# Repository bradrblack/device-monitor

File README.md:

# Device Monitor

A small box that tells you whether a machine is **on or off** by feeling its
vibration: a sump pump, washer, dryer, AC compressor, well pump, dehumidifier.
An ESP32-C3 SuperMini reads an ADXL346 (or ADXL345) accelerometer and reports
every start and stop, with the run length, to whichever of these you use:

- **Web page on the board** (always on): live state, calibration, settings, log.
- **Home Assistant** over MQTT, found automatically (MQTT Discovery). Enables device status voice alerts on smart speakers.
- **ntfy** push notifications to your phone.
- **InfluxDB** (directly or through Telegraf) with a ready-made **Grafana** dashboard.

Everything except the web page is optional and stays off until you configure it.
One firmware image serves every unit: each board's name, Wi-Fi, calibration and
connections are set at run time, not compiled in.

It is the simple sibling of [Sump Master 2000](https://github.com/bradrblack/sump-master-2000)
(which adds water level, temperature and humidity): the same detection algorithm,
reliability code, web page, OTA and outputs, cut down to on/off. The Wi-Fi setup
portal and the case style come from the
[RF ceiling fan remote](https://github.com/bradrblack/rf-ceiling-fan-remote).

**Contents:** [Building a new unit](#building-a-new-unit) ·
[Hardware](#hardware) · [Carrier PCB](#carrier-pcb) · [Case](#case) ·
[Firmware](#firmware) · [First boot and Wi-Fi](#first-boot-and-wi-fi) ·
[Naming the device](#naming-the-device) · [Calibration](#calibration) ·
[Home Assistant](#home-assistant) · [ntfy](#ntfy-notifications) ·
[InfluxDB and Grafana](#influxdb-and-grafana) · [Web page](#web-page) ·
[Updating firmware](#updating-firmware) · [How detection works](#how-detection-works) ·
[Reliability](#reliability) · [Notes](#notes-and-gotchas)

## Building a new unit

The whole path from parts to a calibrated unit on your network:

1. **Pick a case and print it**: [Case](#case). The slide-in case (recommended)
   needs only four soldered wires. The PCB case needs the
   [Carrier PCB](#carrier-pcb) ordered and assembled first.
2. **Wire or assemble the electronics** for that case.
3. **Flash the firmware over USB** (once): [Firmware](#firmware).
4. **Join it to Wi-Fi and name it** with the setup portal from your phone:
   [First boot and Wi-Fi](#first-boot-and-wi-fi).
5. **Close the case and mount it** on the machine (or its pipe), firmly.
6. **Calibrate** on its web page, `http://<name>.local/`: [Calibration](#calibration).
7. **Connect the outputs** you want, on the same page:
   [Home Assistant](#home-assistant), [ntfy](#ntfy-notifications),
   [InfluxDB and Grafana](#influxdb-and-grafana).

After that, updates go over Wi-Fi: [Updating firmware](#updating-firmware).

## Hardware

| Part | Qty | Notes |
|---|---|---|
| ESP32-C3 SuperMini | 1 | The "v2" with an external antenna and an RGB LED on GPIO 8 is the default. An older one with a plain blue LED works too; build `devmon-plain-led` |
| GY-346 module (ADXL346 accelerometer) | 1 | |
| Printed case (tray and lid) | 1 | [Case](#case): slide-in or PCB |
| Thin wire, 26-30 AWG | 4 x 35 mm | Slide-in case only |
| Carrier PCB | 1 | PCB case only: [Carrier PCB](#carrier-pcb) |
| 100-470 µF electrolytic capacitor | 1 | PCB case only, optional: across 3V3/GND next to the accelerometer (max 8 x 12.5 mm, 2.5 mm pitch) |
| USB-C cable and a 5 V USB power supply | 1 | Any phone charger |

**Pins** (the same for both cases):

| Signal | ESP32-C3 | Notes |
|---|---|---|
| Accelerometer SDA | GPIO 5 | I2C at 100 kHz |
| Accelerometer SCL | GPIO 6 | |
| Status LED | GPIO 8 | the SuperMini's own LED |
| 3V3 / GND | 3V3 to VIN, GND to GND | |

GPIO 2, 8 and 9 are boot strapping pins on the C3, so nothing else uses them.

**ADXL345 or ADXL346:** the firmware reads the chip's device ID at boot (0xE5 =
ADXL345, 0xE6 = ADXL346) at either I2C address (0x53 or 0x1D) and uses whichever
it finds; the web page and boot log say which. The two chips are
register-compatible but **not pin-compatible**, and both cases are shaped for the
GY-346 module. An ADXL345 breakout (e.g. GY-291 or Adafruit's) still works
if you wire it by hand to the pins above (VCC to 3V3, CS to 3V3, SDO to GND), as
on the original bench build ([photo](v-sense.jpg)), but it won't fit either case.

**I2C reliability:** keep the connections short (and fit the bulk capacitor on the carrier). On the
Sump Master bench, long jumper wires without a capacitor made the sensor drop out
and the board sometimes crash in the I2C driver on a cold power-up.

## Carrier PCB

Only needed for the PCB case. A 50.5 x 24 mm two-layer carrier holds the SuperMini and the GY-346 module, plus
the bulk capacitor. It is a cut-down of the Sump Master 2000 carrier (same ESP32
and accelerometer placement, same I2C wiring). All parts are through-hole. Three
optional solder jumpers on the back ship open: INT1 to GPIO 4 (not used by this
firmware), CS to 3V3 and SDO to GND (force I2C mode and address 0x53 if a module
misbehaves).

The KiCad project, Gerbers, BOM, assembly steps and the dimensions the case is
built around are in **[hw/PCB.md](hw/PCB.md)**. Upload
`hw/devmon_carrier-v1.0-gerbers.zip` to any PCB fab as a basic 2-layer, 1.6 mm order.

## Case

Two printed cases, both a tray and a lid that click together with no screws and
clamp the accelerometer firmly so it feels the machine:

- **Slide-in case (recommended), 46 x 28 x 15 mm.** No PCB. The SuperMini slides
  into grooves in the walls with its USB-C in the end wall, and the GY-346 sits on
  rails and two pins. Four wires join them (3V3 to VIN, GND, GPIO 5 to SDA, GPIO 6
  to SCL). A flex tab in the lid presses RESET, a row of holes shows the LED, and
  the ribbon antenna sticks to the lid ceiling. Print `hw/case/slide_tray.stl` and
  `hw/case/slide_lid.stl`.
- **PCB case, 56 x 31 x 23 mm.** For the [carrier PCB](#carrier-pcb). Printed pins
  go through the board's holes, lid posts clamp it, and a guide tube over RESET
  takes a paperclip. It fits with or without the bulk capacitor. Print
  `hw/case/tray.stl` and `hw/case/lid.stl`.

Print in PLA or PETG with no supports; a light-coloured lid lets the status LED
show through. Wiring, assembly, the measurements to check before printing and how
to change either case are in **[hw/case/README.md](hw/case/README.md)**.

**Mounting:** the box must move with the machine. Strap or glue it to the motor
housing, the pump's discharge pipe or a rigid panel, not to something that damps
vibration (a hose, foam, a wobbly cover). A cable tie that's tight on a pipe works
well. Then calibrate in place.

## Firmware

Built with [PlatformIO](https://platformio.org/) (VS Code extension or the `pio`
command line), the same toolchain as Sump Master 2000 (pioarduino platform
55.03.37, Arduino core 3.3).

1. **Get the code** and create the one required local file:
   ```
   git clone https://github.com/bradrblack/device-monitor
   cd device-monitor
   cp secrets.ini.example secrets.ini
   ```
   Set `ota_password` in `secrets.ini` (letters and digits). It authenticates
   OTA uploads from PlatformIO and is every new board's first **admin password**
   for its web page. `secrets.ini` is git-ignored.

   `src/secrets.h` is **optional**: copy `src/secrets.h.example` only if you
   want new boards to start with your Wi-Fi, ntfy topic, InfluxDB or MQTT
   already filled in. Everything in it can be set on the board instead.
2. **Plug the SuperMini in by USB and flash** (this also installs the OTA
   partition table, which can't be changed over the air):
   ```
   pio run -t upload
   ```
   (For a SuperMini with a plain blue LED: `pio run -e devmon-plain-led -t upload`.)
   If the upload can't find the board, hold BOOT, tap RESET, release BOOT, and try again.
3. **Watch it boot** (optional): `pio device monitor`. You'll see the banner,
   the accelerometer it found (`ADXL346 detected at 0x53`), and Wi-Fi.

## First boot and Wi-Fi

A new board has no Wi-Fi network saved, so it opens a **setup portal**:

1. The LED turns **purple**. On your phone, join the Wi-Fi network
   **`DeviceMonitor-XXXX`** (open, no password). The setup page usually pops up
   by itself; if not, browse to `http://192.168.4.1/`.
2. Tap **Configure WiFi**, pick your network and type its password.
3. Fill in **Device name** (see [Naming the device](#naming-the-device)) and,
   optionally, a **new admin password** (8+ characters) to replace the OTA
   password from `secrets.ini`.
4. **Save.** The board joins your network (and restarts once if you named it).
   The LED turns **green**. Your phone goes back to its normal network.
5. Open **`http://<name>.local/`** (e.g. `http://sump.local/`). If `.local`
   names don't resolve on your network (some Android phones, some Windows
   setups), use the IP address from your router's client list or the serial log.

The portal also opens:

- **Only on a board with no network saved.** Once a network is saved, the board
  never opens the portal by itself: if it can't join (router restarting, power cut
  that outlasts the router), it keeps retrying the saved network every 30 s and
  rejoins as soon as the router is back. If the portal does open on a new board
  and nobody uses it, it closes after 5 minutes and the board restarts.
- **On demand**: press **RESET twice**, about a second apart: the flex tab on the
  slide-in lid, or a paperclip through the PCB case's lid. (The LED flashes white for the first 5 seconds after any reset; a
  second press in that time opens the portal.) Or use **Change Wi-Fi network**
  on the web page.

On a board that already has a network, the on-demand portal never takes it
offline. The board joins its saved network first and keeps monitoring and
reporting while the portal is open beside it (the LED stays purple). If nobody
uses the portal, it closes after 5 minutes and the board carries on as before. The
board's own web page is unavailable while the portal is open, because both use
port 80. This matters because the C3 can't tell a RESET press from a power
cycle, so two power bumps a few seconds apart look like a double press. With
this design they just open a portal nobody uses.

If you put `WIFI_SSID` / `WIFI_PASS` in `src/secrets.h`, a new board tries that
network first and only opens the portal if it can't join (and nothing is saved yet).

## Naming the device

The name is the board's identity everywhere: its network name (`<name>.local`),
ntfy titles (`sump started`), the InfluxDB `device` tag, and the Home Assistant
device and MQTT topics (`devmon/<name>/...`). Use lowercase letters, digits and
`-`, up to 24 characters, e.g. `sump`, `washer`, `dryer`, `ac-upstairs`. Until
you name it, a board calls itself `devmon-XXXX` (the end of its MAC address).

Set it in the setup portal, or later under **Device** on the web page (with the
time zone). Renaming restarts the board under its new address and removes the
old name's Home Assistant entries. InfluxDB keeps the old name's history under
the old tag.

## Calibration

Every machine and mounting is different, so each unit needs its two vibration
thresholds set once. The web page has a guided calibration:

1. With the machine **off** (and the house as busy as it usually is), press
   **Measure idle (30 s)**.
2. With the machine **running** normally, press **Measure running (30 s)**.
3. Press **Use suggested thresholds**, check the numbers and **Save** (log in
   first, user `admin` and the admin password).

The suggestion puts both thresholds between the loudest idle moment and the
quietest running moment (start at 60% and stop at 30% of the gap). If the running
level dips close to idle now and then (a microwave, a washer pausing), it uses the
running **average** instead (start at 50%, stop at 25% of the gap), and if idle
bumps reach the running level it measures from the idle average; the start and
stop delays ride out those short overlaps. If the page still says running is too
close to idle, mount the box more firmly or closer to the motor and measure again.

| Setting | Default | Meaning |
|---|---|---|
| Start threshold | 0.50 m/s² RMS | vibration above this counts towards a start |
| Stop threshold | 0.30 m/s² RMS | vibration below this counts towards a stop |
| Seconds of vibration to count as started | 3 | continuous, so footsteps and bumps don't count |
| Seconds of quiet to count as stopped | 3 | **raise it for machines that pause mid-cycle** |

A pump or compressor is simply on or off, so 3 s each is right. A **washer**
pauses inside a cycle (filling, soaking), and a **dryer** may tumble in bursts:
set "seconds of quiet" to a few minutes (e.g. 300) or one cycle is reported as
several. The page's chart shows live vibration against both thresholds, and the
"Passive" lines keep the idle peak and the last run's lowest value since the last
restart, so you can check the calibration after a few real runs. With InfluxDB,
the Grafana panel "Vibration: idle and running, against the thresholds" shows
the same over days.

Settings are stored on the board and survive restarts and firmware updates.
**Reset to defaults** returns to the values in `platformio.ini`.

## Home Assistant

1. In Home Assistant, install an MQTT broker (the **Mosquitto** add-on) and the
   **MQTT** integration. The add-on needs a login: use a Home Assistant user, or
   add one in the add-on's configuration.
2. On the board's web page, under **Connections**, enter the broker's address
   (host name or IP, no `mqtt://`), port 1883, user name and password. **Save
   connections.** The line at the top of the card shows "Home Assistant (MQTT)
   connected", or why not.
3. The device appears under **Settings > Devices & services > MQTT**, named after
   the board.

| Entity | Notes |
|---|---|
| Running | binary sensor (device class *running*), sent the moment it changes |
| Vibration | m/s² RMS, every 30 s |
| Last run | seconds |
| Runs since restart | |
| Accelerometer | problem sensor (diagnostic) |
| Wi-Fi signal, Uptime, Firmware | diagnostic |

Topics: `devmon/<name>/state` (retained JSON), `devmon/<name>/status`
(`online`/`offline`; the broker sends `offline` if the board disappears, so the
entities go unavailable), and `homeassistant/<type>/devmon_<name>/<entity>/config`
for discovery. For "tell me when the washer finishes", make an automation on
Running turning off.

## ntfy notifications

[ntfy](https://ntfy.sh) pushes to your phone with no account. Install the ntfy
app, subscribe to a topic name that is **random and unguessable** (topics are
public to anyone who knows the name), and enter the same topic under
**Connections** on the web page. The server defaults to `https://ntfy.sh`;
change it if you run your own.

| Push | Priority |
|---|---|
| `<name> started` / `<name> stopped (ran 28.8 s)` (checkbox "Push on every start and stop") | default |
| Daily report just before the 3 AM restart: state, runs and run time for the day, firmware (checkbox "Daily report push"; doubles as a heartbeat) | low |
| Accelerometer not responding, and back | high / default |
| InfluxDB unreachable for 30 minutes, and back | default |
| Unexpected reboots with the reason, e.g. `sump rebooted: WiFi down watchdog (reboot #2)` | default |
| Firmware updated / rolled back | default / high |

**Send a test** on the web page sends a test push. Pushes are queued and retried
if the internet is down. ntfy.sh limits anonymous use per IP per day; a busy
washer is a few pushes per cycle, which is fine.

## InfluxDB and Grafana

The board sends InfluxDB line protocol over HTTP, timestamped with its own
NTP-synced clock, so delayed points land at the right time. Points queue on the
board (150 lines, about a day) while the server is unreachable. Two ways in:

- **Directly to InfluxDB 2.x:** address
  `http://<server>:8086/api/v2/write?org=<org>&bucket=<bucket>&precision=ns` and
  a **write-only token** for that bucket.
- **Through Telegraf** (`telegraf/devmon.conf`): address
  `http://<server>:8186/devmon`, no token on the board. Use this if you already
  run Telegraf or don't want tokens on the boards.

Enter it under **Connections** and press **Send a test**: an `appliance_test`
point should appear in InfluxDB's Data Explorer within a few seconds. If not,
the board's log says `[influx] ...` with the error (`connection refused` = wrong
address or port, HTTP 401 = bad token).

### Setting up InfluxDB and Grafana (Docker)

Skip this if you already run them. On any always-on machine on your network
(Raspberry Pi, NAS, home server) with [Docker](https://docs.docker.com/get-docker/),
create `docker-compose.yml` (change the passwords and token):

```yaml
services:
  influxdb:
    image: influxdb:2
    restart: unless-stopped
    ports: ["8086:8086"]
    volumes: ["influx-data:/var/lib/influxdb2"]
    environment:
      DOCKER_INFLUXDB_INIT_MODE: setup
      DOCKER_INFLUXDB_INIT_USERNAME: admin
      DOCKER_INFLUXDB_INIT_PASSWORD: change-this-password
      DOCKER_INFLUXDB_INIT_ORG: home
      DOCKER_INFLUXDB_INIT_BUCKET: devmon
      DOCKER_INFLUXDB_INIT_ADMIN_TOKEN: change-this-admin-token

  grafana:
    image: grafana/grafana-oss
    restart: unless-stopped
    ports: ["3000:3000"]
    depends_on: [influxdb]
    volumes: ["grafana-data:/var/lib/grafana"]

volumes:
  influx-data:
  grafana-data:
```

Run `docker compose up -d`. Then:

1. **Tokens.** In InfluxDB (`http://<server>:8086`, user `admin`): **Load Data >
   API Tokens > Generate API Token > Custom API Token**. Make one with **Write**
   access to the `devmon` bucket (for the boards) and one with **Read** access
   (for Grafana).
2. **Boards.** On each board's web page, InfluxDB address
   `http://<server>:8086/api/v2/write?org=home&bucket=devmon&precision=ns` and the
   write token. **Save connections**, then **Send a test**.
3. **Grafana data source.** Grafana is at `http://<server>:3000` (first login
   `admin`/`admin`). **Connections > Data sources > Add data source > InfluxDB**:
   query language **Flux**, URL `http://influxdb:8086`, organisation `home`,
   default bucket `devmon`, the **read** token. **Save & test.**
4. **Dashboard.** **Dashboards > New > Import**, upload
   `grafana/appliance-monitor.json`, pick the data source, then set the `bucket`
   variable to `devmon` in the dashboard settings. Every board shows up by its
   name; the `device` drop-down filters them.

Prefer Telegraf? Add a `telegraf` service with `./devmon.conf` mounted as
`/etc/telegraf/telegraf.conf`, port `8186`, and the variables from
`telegraf/devmon.env.example` (with the write token), and point the boards at
`http://<server>:8186/devmon`.

**Dashboard panels:** on/off timeline, current state, run time per day, runs per
day, recent runs, time since each board's last data, vibration against the
thresholds, Wi-Fi signal, reboots; reboots and threshold changes are also
annotations on every graph.

**"Device monitor silent" alert** (`grafana/devmon-alerting.yaml`): an ntfy push
when any board has sent nothing for 30 minutes (power, Wi-Fi, a hang), which the
board can't report itself. Fill in the three `CHANGE_ME` values, copy it to
Grafana's `provisioning/alerting/` directory and restart Grafana. (With Home
Assistant alone, make an automation on the device becoming unavailable instead.)

### Data

All points are tagged `device=<name>`.

| Measurement | When | Fields |
|---|---|---|
| `appliance_state` | each start/stop | `event` (`start`/`stop`), `running` (1/0), `seconds` (stop), `rms_avg`, `rms_min` (stop: that run's vibration); `note="restart"` on a post-reboot correction, `note="sensor_lost"` if the accelerometer dropped out mid-run |
| `appliance_reading` | every 10 min, on the clock | `running`, `sensor_ok`, `cycles` and `run_s` for the 10 minutes, `rssi`, `heap`, `rms_idle_avg`, `rms_idle_max`, `rms_run_avg`, `rms_run_min`, and the thresholds `rms_on`, `rms_off` |
| `appliance_boot` | each boot | `version`, `reason`, `sensor` |
| `appliance_config` | thresholds changed | `rms_on`, `rms_off`, `run_confirm_s`, `stop_confirm_s` |
| `appliance_test` | "Send a test" | `value` |

`appliance_state` keeps the field names of the earlier Adafruit IO version, so
history recorded through the old Telegraf bridge stays on the same dashboard.

## Web page

`http://<name>.local/` from any phone or computer on your network:

- **Live state**: running or off, vibration, the current run's length, runs and
  run time since restart, and a chart of the last few minutes against both
  thresholds.
- **Calibrate**: the guided idle/running measurement above.
- **Detection settings**, **Device** (name, time zone), **Connections**
  (InfluxDB, ntfy, MQTT, admin password, Send a test).
- **Maintenance**: firmware upload, Change Wi-Fi network, Restart.
- **Log**: the last 120 log lines.

Viewing needs no password; anyone on your network can see the state and the log.
To change anything, first press **Log in** at the top of the page: the browser asks
for user `admin` and the admin password (HTTP digest authentication, so the password
itself isn't sent) and the board gives it a session cookie for the saves that
follow. A restart, or a new admin password, logs everyone out. From a script, send
the digest login with each request instead, e.g.
`curl --digest -u admin:<password> -d "mqtt_host=..." http://<name>.local/connections`.
What you type into a form (an
MQTT password, a token) does cross your network unencrypted, since the page is
plain HTTP. Saved secrets are never shown back. The page isn't reachable from the
internet unless you set that up yourself.

Scripting: `GET /api/status` (JSON) and `GET /api/log?since=N` (text; the first
line is the count to pass back as `since`).

## Updating firmware

After the first USB flash, either:

- **From PlatformIO over Wi-Fi:**
  `pio run -e devmon-ota -t upload --upload-port <name>.local`
  (uses `ota_password` from `secrets.ini`; set `ota_host` there to skip the flag
  for your usual board). Only accepted while the machine is idle, because an
  upload pauses sampling for about 15 s; if it fails with no response, run it
  again once the machine stops.
- **From the web page:** build with `pio run`, then under **Maintenance** upload
  `.pio/build/devmon/firmware.bin` (admin password).

Either way the new firmware runs as a **trial**: after 3 minutes with Wi-Fi up and
the accelerometer answering (if it was before), it's marked good and ntfy says
`<name> updated A -> B`. If it isn't healthy within 10 minutes, crashes, or
restarts during the trial, the board goes back to the previous firmware by itself
and ntfy says `update rolled back`. Last resort: flash over USB.

Bump `FIRMWARE_VERSION` in `src/device-monitor.ino` for each release.

## How detection works

- Samples the accelerometer at 400 Hz (±16 g, full resolution) and high-passes
  each axis against a slow baseline (about 13 Hz cutoff). That removes gravity and
  the mounting angle, and rejects footsteps and house rumble, while passing motor
  vibration (29-58 Hz for 1725/3450 RPM motors).
- RMS over 250 ms windows.
- A run **starts** after "seconds of vibration" of continuous windows above the
  start threshold and **stops** after "seconds of quiet" of continuous windows
  below the stop threshold. Between the two thresholds is a hysteresis band that
  counts towards neither, so impulsive bumps don't start a run and a motor
  dipping briefly doesn't end one. Events carry the time the vibration really
  started or stopped, not when it was confirmed.
- Every window is filed as idle or running (windows during a confirmation wait
  until it's known which), which is what the passive calibration readings and the
  Grafana vibration panel show.

**LED** (v2 RGB LED): **green** idle, **yellow** vibration seen but not (yet) a run,
**blue** running, **flashing red** accelerometer missing, **purple** setup portal
open, **flashing white** the 5 seconds after a reset (press RESET again now for
the portal). With a plain LED: off idle, on vibration seen, slow blink running,
fast blink accelerometer missing, on while the portal is open.

Serial (115200) prints a status line each second:
`rms=0.208 max=0.219 loud=0 state=idle wifi=up iq=0` (`max` the loudest window
of that second, `loud` how many windows reached the stop threshold, `iq` points
waiting for InfluxDB).

## Reliability

Ported from Sump Master 2000: recover on its own where possible, never fail silently.

| Mechanism | Behavior |
|---|---|
| **Wi-Fi at boot** | Saved network tried for 30 s; if that fails the board starts anyway and keeps retrying every 30 s (no automatic portal once a network is saved; double-press RESET for it, and the board stays online while it's open). A new board with no network opens the portal for 5 minutes, then restarts. |
| **Wi-Fi watchdog** | If Wi-Fi drops it resets the radio and retries every 30 s; if it stays down for 2 minutes, it restarts. |
| **Accelerometer watchdog** | Every 30 s the chip's device ID and measure mode are checked (a dead sensor otherwise reads as zeros, which looks like a machine that's off). Missing at boot or after three failed checks, failing reads, or a perfectly flat signal: detection pauses, a run in progress is closed with `note="sensor_lost"`, one push says so, and it's retried every 30 s with I2C bus recovery (clocking SCL to release a stuck bus). A push says when it's back. The web page and OTA keep working. |
| **Outputs** | InfluxDB, ntfy and MQTT failures never restart the board: data queues and is retried, and one push reports a long InfluxDB outage. |
| **Task watchdog** | A 30 s hardware watchdog resets a hung main loop; the reset is reported on the next boot. |
| **Nightly restart** | 3 AM local time, after the daily report, against slow heap fragmentation. Held off while the machine runs, a push is waiting, a calibration is running or an OTA trial is in progress. The day is stored in flash so it can't loop within the hour. |
| **Unexpected reset detection** | A crash, watchdog or brownout reset is detected on the next boot and pushed with the reason and a count. Power cycles, the reset button, flashing and deliberate restarts are not. |
| **Stuck "running" correction** | If the board restarts mid-run and the machine is idle 15 s after boot, a `stop` (with `note="restart"`, no run length) is recorded so nothing implies it's still running. |
| **OTA rollback** | See [Updating firmware](#updating-firmware). |

## Notes and gotchas

- **Toolchain:** the platform is pinned to pioarduino `55.03.37` (as in Sump
  Master 2000) because the unpinned "stable" release's esptool crashed mid-upload;
  don't unpin it.
- **Wi-Fi TX power** is capped at 15 dBm. Older SuperMinis joined Wi-Fi on only
  about 1 boot in 3 at full power; the v2 boards don't need it, but it's harmless.
  If a board is flaky joining, lower `WIFI_TX_POWER` to `WIFI_POWER_8_5dBm`.
- The OTA password (in `secrets.ini`) is compiled in and stays the password for
  PlatformIO uploads; the web page's admin password starts as the same value and
  can be changed separately.
- The USB port name changes each time the board re-enumerates; close any serial
  monitor before flashing.
- Log lines are timestamped (wall-clock time once NTP syncs, uptime before that).

### Upgrading from the Adafruit IO version

Earlier versions (up to 2026-09-22r1) published to an Adafruit IO feed and set the
device name and thresholds per PlatformIO environment (`pump`, `dryer`). This
version drops Adafruit IO in favour of direct InfluxDB/Telegraf, ntfy and MQTT.
To move an existing board: flash it over USB once (`pio run -t upload`, which also
installs the OTA partition table), set its Wi-Fi and the same name (`pump`) in
the setup portal, and enter its old thresholds on the web page (the pump used
start 0.40 / stop 0.20). Replace the old Adafruit IO Telegraf bridge with
`telegraf/devmon.conf` (or write directly to InfluxDB); the dashboard keeps the
old history because the measurement and field names are unchanged.

## Future ideas

### Battery-powered version (deep sleep + accelerometer wake)

The carrier PCB has a solder jumper (JP1, open) from the ADXL346's INT1 to GPIO 4,
a deep-sleep wake pin, for this. The idea: the ESP32 deep-sleeps while the
accelerometer watches for motion (about 25 µA) on its activity interrupt; on wake,
sample ~3 s with the normal detection and go back to sleep on a false alarm; on a
confirmed run, report the start and re-arm the chip for an *inactivity* interrupt.
To sort out first: the SuperMini's own sleep current (USB chip, LED, regulator),
false wakes from footsteps, and the Wi-Fi join cost per event.

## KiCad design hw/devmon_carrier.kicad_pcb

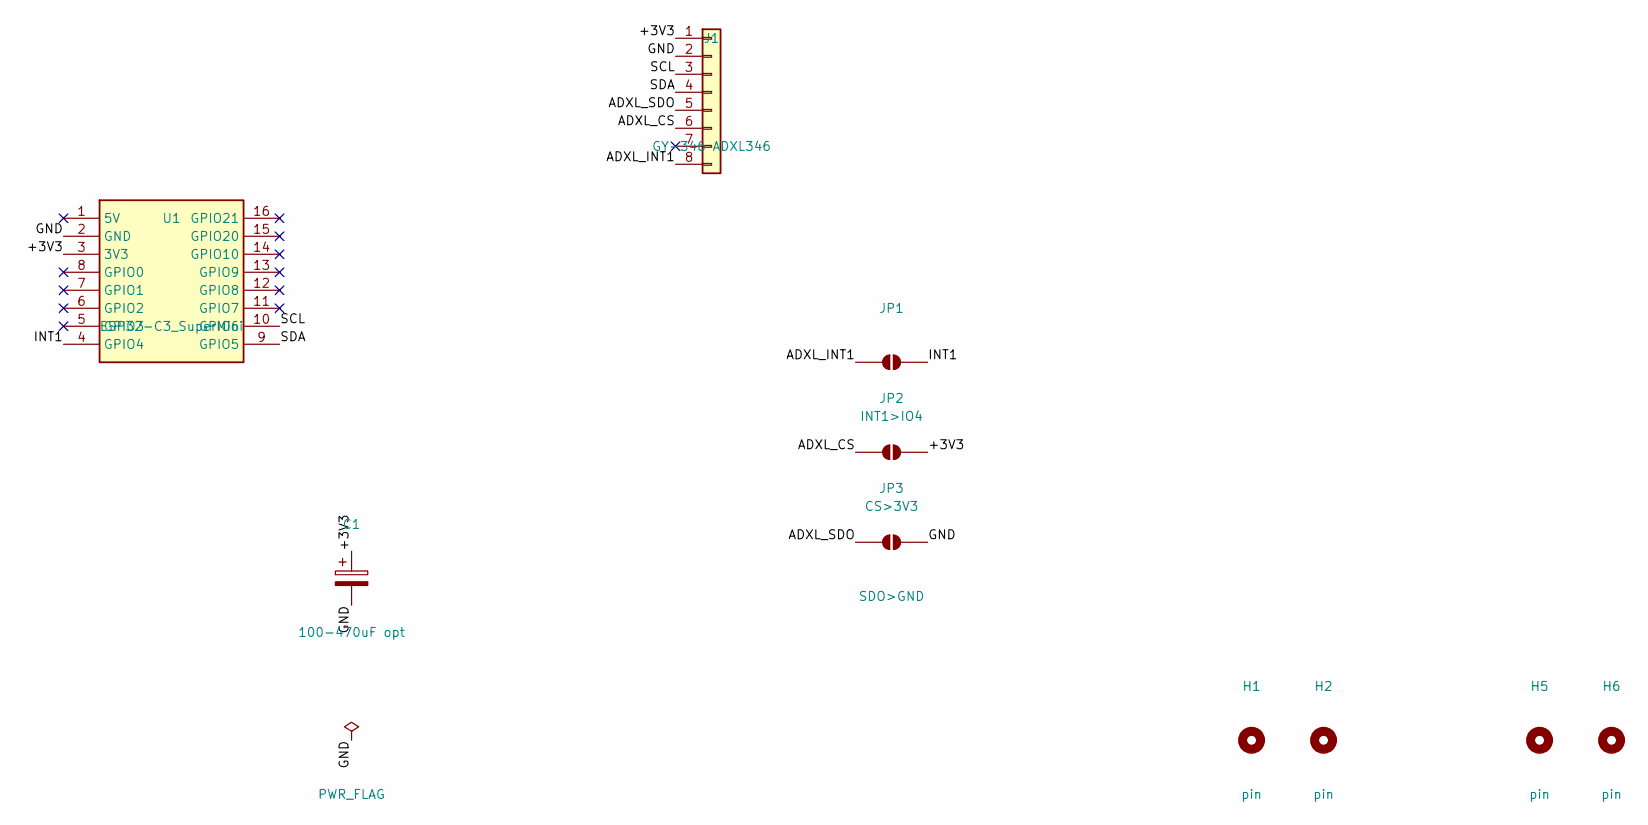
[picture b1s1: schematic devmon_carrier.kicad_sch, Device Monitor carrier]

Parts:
C1: 100-470uF opt; CP_Radial_D8.0mm_P2.50mm
H1, H2, H5, H6: pin; CasePin_Hole_2.5mm
J1: GY-346 ADXL346; PinHeader_1x08_P2.54mm_Vertical
JP1: INT1>IO4; SolderJumper-2_P1.3mm_Open_RoundedPad1.0x1.5mm
JP2: CS>3V3; SolderJumper-2_P1.3mm_Open_RoundedPad1.0x1.5mm
JP3: SDO>GND; SolderJumper-2_P1.3mm_Open_RoundedPad1.0x1.5mm
U1: ESP32-C3_SuperMini; ESP32-C3_SuperMini_FaceUp

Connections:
/+3V3: C1.1, J1.1, JP2.2 (B), U1.3 (3V3)
/ADXL_CS: J1.6, JP2.1 (A)
/ADXL_INT1: J1.8, JP1.1 (A)
/ADXL_SDO: J1.5, JP3.1 (A)
/GND: C1.2, J1.2, JP3.2 (B), U1.2 (GND)
/INT1: JP1.2 (B), U1.4 (GPIO4)
/SCL: J1.3, U1.10 (GPIO6)
/SDA: J1.4, U1.9 (GPIO5)

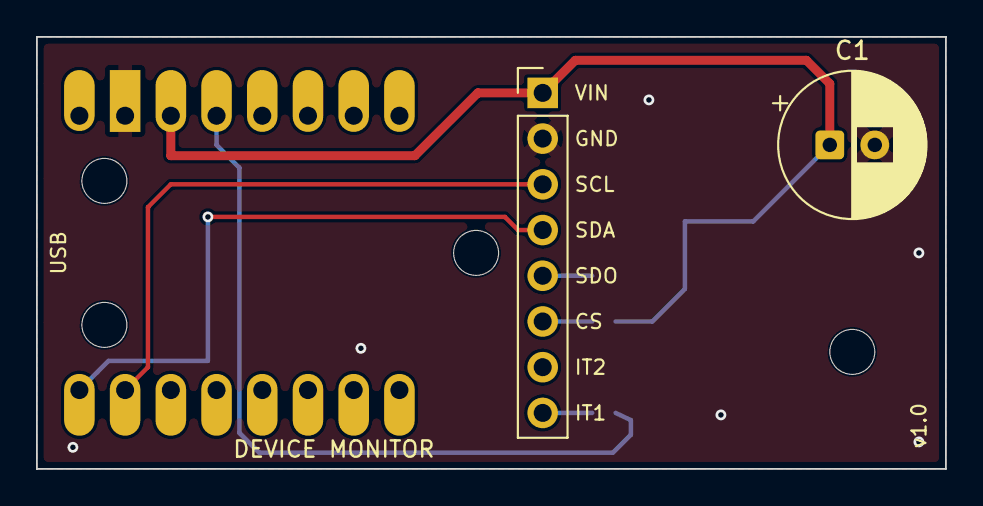
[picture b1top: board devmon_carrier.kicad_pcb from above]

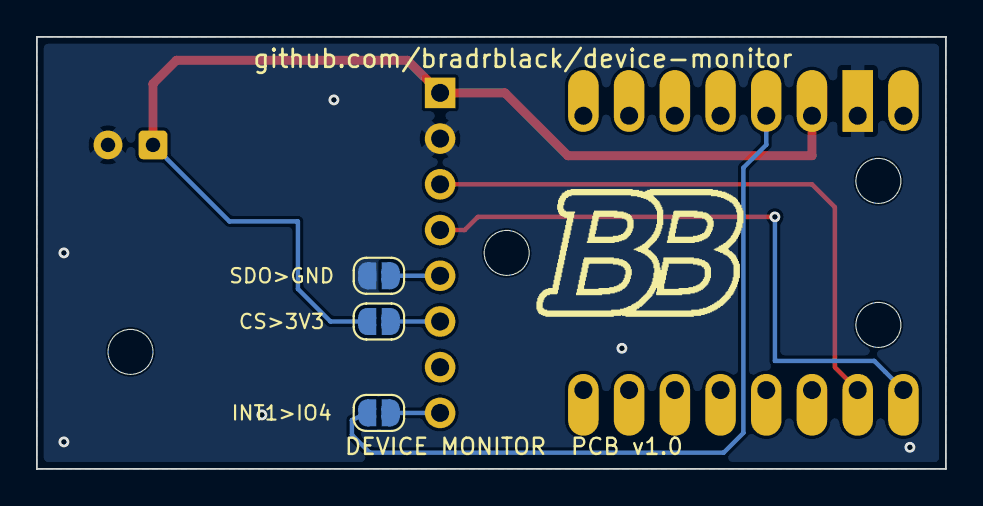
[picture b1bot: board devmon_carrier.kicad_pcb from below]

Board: 2 copper layers, 50.5 x 24.0 mm, 10 parts (3 on the bottom side), 8 nets.
